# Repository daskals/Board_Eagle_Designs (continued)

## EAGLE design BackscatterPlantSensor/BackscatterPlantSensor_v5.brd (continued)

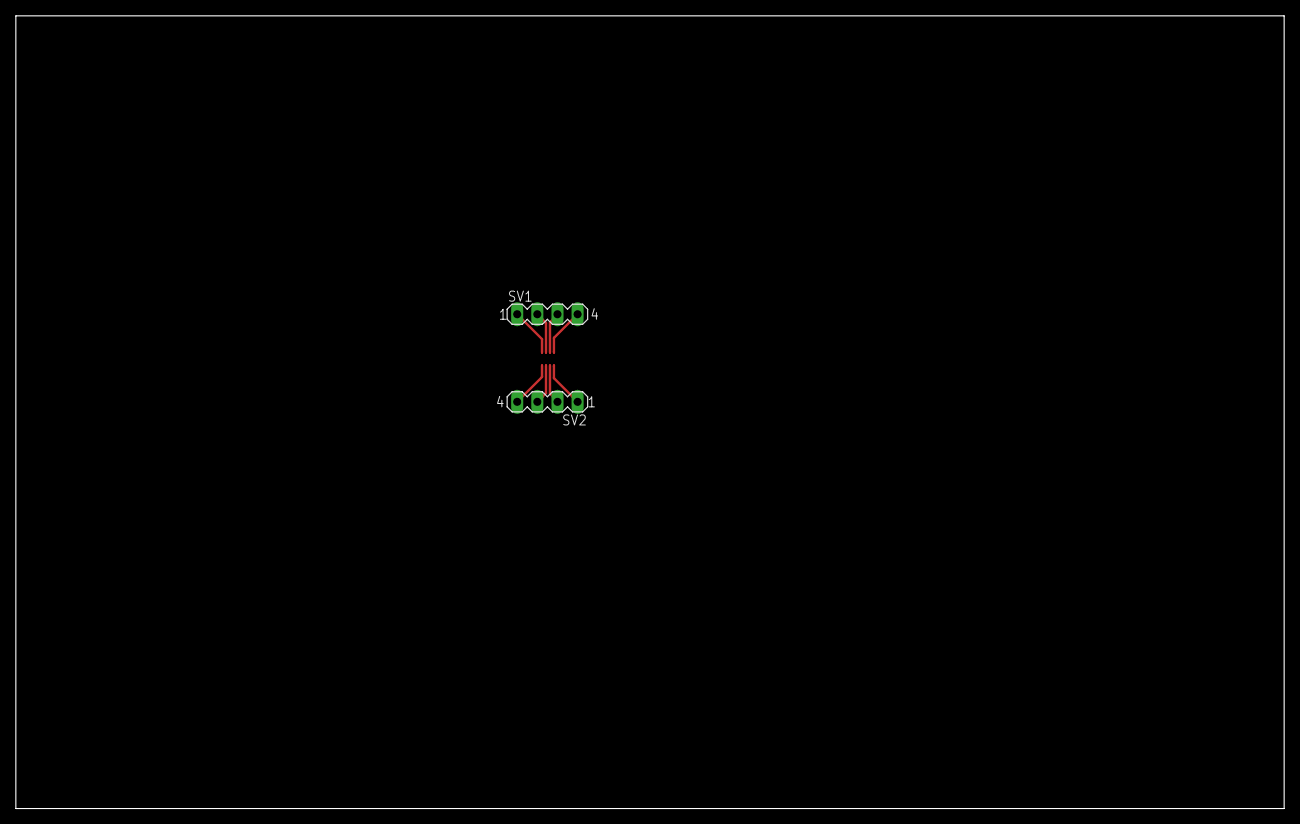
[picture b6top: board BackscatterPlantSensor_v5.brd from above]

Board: 2 copper layers, 160.0 x 100.0 mm, 3 parts (0 on the bottom side), 8 nets.
